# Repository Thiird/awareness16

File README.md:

# Awareness16
Mechanical macropad, used as pathfinder for my first custom mechanical keyboard build.  

**SPECS**  
-16 1U keys in a 4x4 matrix, MX footprint

-USB C, CtoC compatible

-RGB Matrix, 6028 SMD LEDs 

-RGB underglow, SK6812MINI-E SMD LEDs

-ESD protection

-MCU: Atmega 32u4, TQFP44 package

-LED driver: IS31FL3733, eTQFP-48 package

# Renderings

**PCB top**

**PCB bottom**

# Credits
Without the help of many generous and patient people online I would have never been able to complete
this project.

Special thanks to:
- Hadi for making a pcb guide series: https://www.youtube.com/channel/UCpWGAJr2AU7LPUwVYbBQZRg
- People on the Keyboard Atelier discord
- People on the QMK discord

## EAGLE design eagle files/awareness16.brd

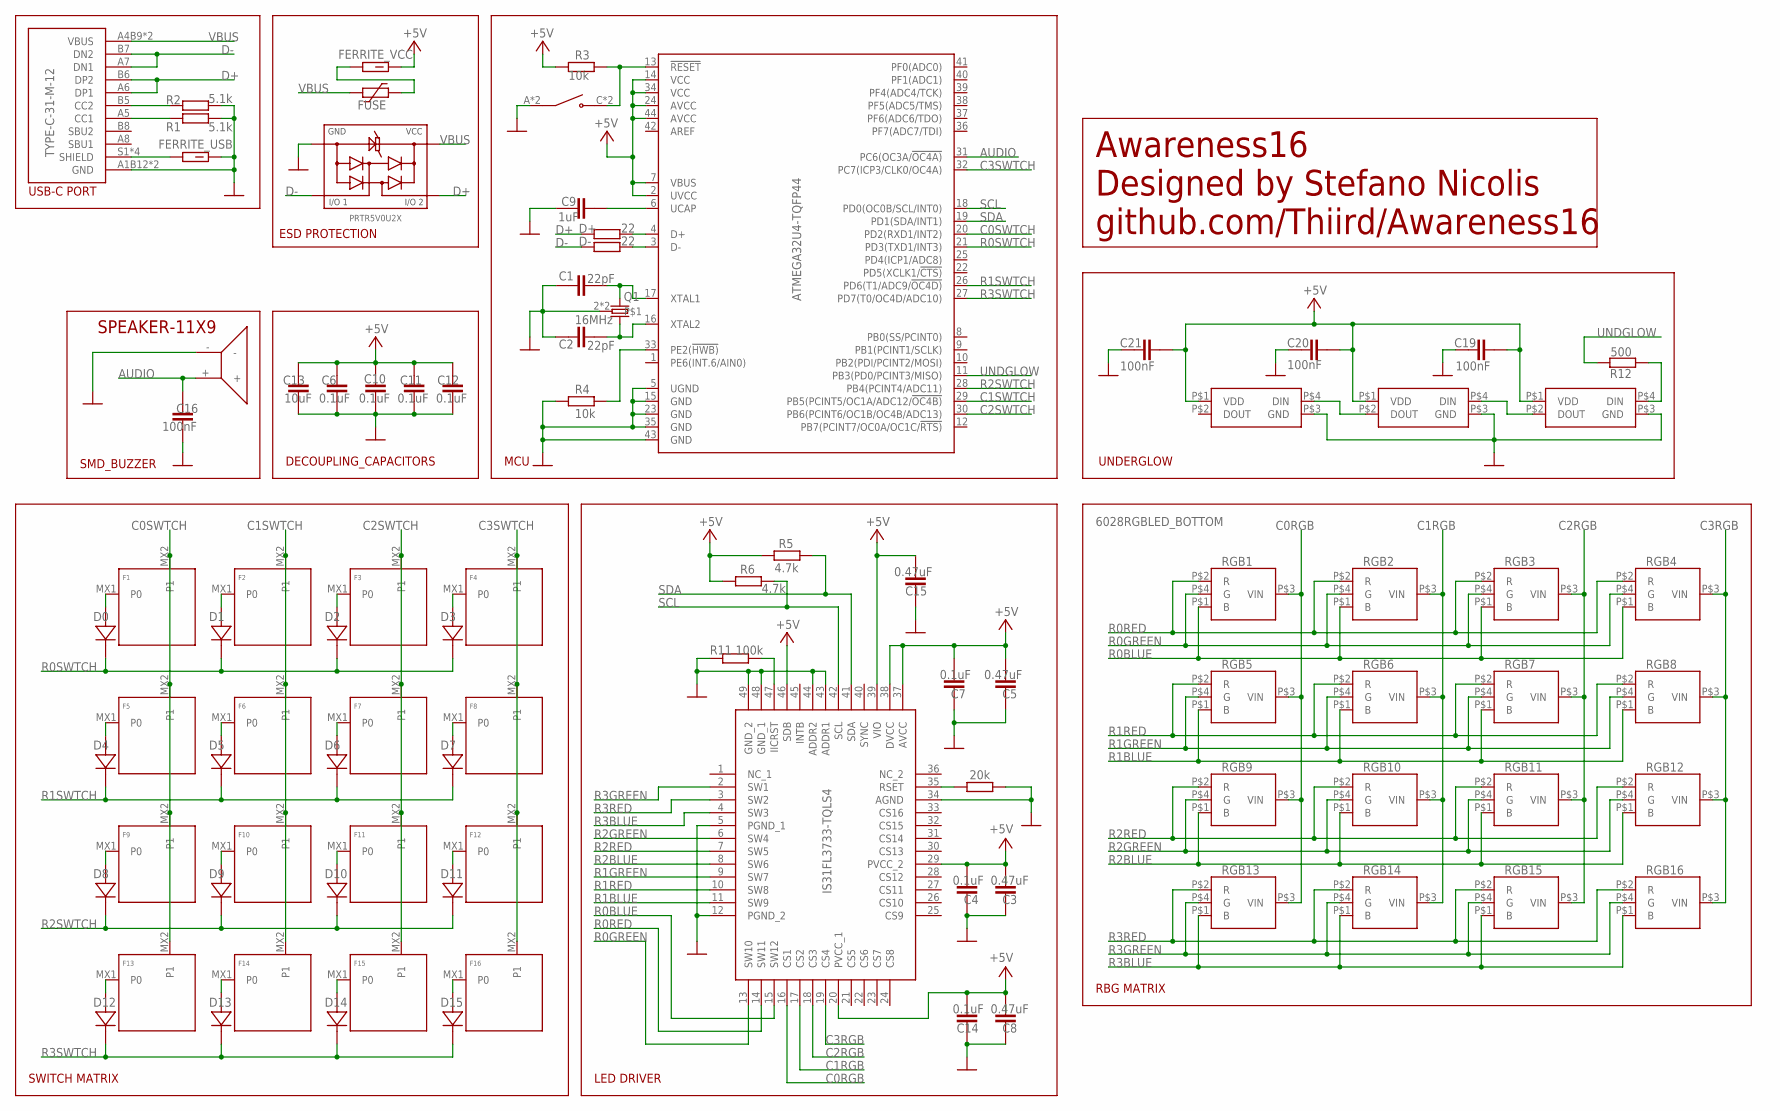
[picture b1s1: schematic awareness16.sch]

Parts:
C1, C2: 22pF; C0603
C3, C5, C8, C15: 0.47uF; C0603
C4, C6, C7, C10, C11, C12, C14: 0.1uF; C0603
C9: 1uF; C0603
C13: 10uF; C0603
C16, C19, C20, C21: 100nF; C0603
D0, D1, D2, D3, D4, D5, D6, D7, D8, D9, D10, D11, D12, D13, D14, D15: DIODE-SOD-123; SOD-123
D+: 22; R0603
D-: 22; R0603
DRIVER: IS31FL3733-TQLS4; QFP50P900X900X120-49N
F1, F2, F3, F4, F5, F6, F7, F8, F9, F10, F11, F12, F13, F14, F15, F16: KEYSWITCH-PLAIN-MX-1U; MX-1U
FERRITE_USB: FERRITE_BEAD; BEADC1608X95N
FERRITE_VCC: FERRITE_BEAD; BEADC1608X95N
FUSE: 0603L050; 0603L
J1: TYPE-C-31-M-12; HRO_TYPE-C-31-M-12
MCU: ATMEGA32U4-TQFP44; TQFP44-0.8-9.6X9.6MM
Q1: 16MHz; 2.0X1.6_KX-5
R1, R2: 5.1k; R0603
R3, R4: 10k; R0603
R5, R6: 4.7k; R0603
R11: 100k; R0603
R12: 500; R0603
RESET: 20k; R0603
RGB1, RGB2, RGB3, RGB4, RGB5, RGB6, RGB7, RGB8, RGB9, RGB10, RGB11, RGB12, RGB13, RGB14, RGB15, RGB16: 6028RGBLED_BOTTOM
S1: TS-1187A-B-A-B; SW_TS-1187A-B-A-B
SP1: SPEAKER-11X9; AST1109MLTRQ
U$1: PRTR5V0U2X
UGLOW1, UGLOW2, UGLOW3: SK6812MINI-E

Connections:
AUDIO: C16.1, MCU.31 (PC6(OC3A/!OC4A)), SP1.+
C0RGB: DRIVER.16 (CS1), RGB1.P$3 (VIN), RGB5.P$3 (VIN), RGB9.P$3 (VIN), RGB13.P$3 (VIN)
C0SWTCH: F1.MX2 (P1), F5.MX2 (P1), F9.MX2 (P1), F13.MX2 (P1), MCU.20 (PD2(RXD1/INT2))
C1RGB: DRIVER.17 (CS2), RGB2.P$3 (VIN), RGB6.P$3 (VIN), RGB10.P$3 (VIN), RGB14.P$3 (VIN)
C1SWTCH: F2.MX2 (P1), F6.MX2 (P1), F10.MX2 (P1), F14.MX2 (P1), MCU.29 (PB5(PCINT5/OC1A/ADC12/!OC4B))
C2RGB: DRIVER.18 (CS3), RGB3.P$3 (VIN), RGB7.P$3 (VIN), RGB11.P$3 (VIN), RGB15.P$3 (VIN)
C2SWTCH: F3.MX2 (P1), F7.MX2 (P1), F11.MX2 (P1), F15.MX2 (P1), MCU.30 (PB6(PCINT6/OC1B/OC4B/ADC13))
C3RGB: DRIVER.19 (CS4), RGB4.P$3 (VIN), RGB8.P$3 (VIN), RGB12.P$3 (VIN), RGB16.P$3 (VIN)
C3SWTCH: F4.MX2 (P1), F8.MX2 (P1), F12.MX2 (P1), F16.MX2 (P1), MCU.32 (PC7(ICP3/CLK0/OC4A))
D+: D+.1, J1.A6 (DP1), J1.B6 (DP2), U$1.3
D-: D-.1, J1.A7 (DN1), J1.B7 (DN2), U$1.2
GND: C1.1, C2.1, C3.1, C4.1, C5.1, C6.2, C7.1, C8.1, C9.1, C10.2, C11.2, C12.2, C13.2, C14.1, C15.1, C16.2, C19.1, C20.1, C21.1, DRIVER.5 (PGND_1), DRIVER.12 (PGND_2), DRIVER.34 (AGND), DRIVER.43 (ADDR1), DRIVER.44 (ADDR2), DRIVER.48 (GND_1), DRIVER.49 (GND_2), FERRITE_USB.2, J1.A1B12 (GND), J1.B1A12 (GND), MCU.5 (UGND), MCU.15 (GND), MCU.23 (GND), MCU.35 (GND), MCU.43 (GND), Q1.2, Q1.4, R1.1, R2.1, R4.1, R11.1, RESET.2, S1.A (COM), S1.B (COM), SP1.-, U$1.1, UGLOW1.P$3 (GND), UGLOW2.P$3 (GND), UGLOW3.P$3 (GND)
unnamed: D0.A, F1.MX1 (P0)
unnamed: FERRITE_VCC.1, FUSE.1
unnamed: D1.A, F2.MX1 (P0)
unnamed: D2.A, F3.MX1 (P0)
unnamed: C2.2, MCU.16 (XTAL2), Q1.3 (2)
unnamed: D-.2, MCU.3 (D-)
unnamed: R12.1, UGLOW3.P$4 (DIN)
unnamed: MCU.33 (PE2(!HWB)), R4.2
unnamed: D4.A, F5.MX1 (P0)
unnamed: DRIVER.47 (IICRST), R11.2
unnamed: D5.A, F6.MX1 (P0)
unnamed: D6.A, F7.MX1 (P0)
unnamed: D9.A, F10.MX1 (P0)
unnamed: D+.2, MCU.4 (D+)
unnamed: MCU.13 (!RESET), R3.2, S1.C (NO), S1.D (NO)
unnamed: C9.2, MCU.6 (UCAP)
unnamed: C1.2, MCU.17 (XTAL1), Q1.1
unnamed: D10.A, F11.MX1 (P0)
unnamed: FERRITE_USB.1, J1.A5 (CC1), J1.B5 (CC2), J1.S1 (SHIELD), J1.S2 (SHIELD), J1.S3 (SHIELD), J1.S4 (SHIELD), R1.2, R2.2
unnamed: UGLOW1.P$4 (DIN), UGLOW2.P$2 (DOUT)
unnamed: DRIVER.35 (RSET), RESET.1
unnamed: D3.A, F4.MX1 (P0)
unnamed: D7.A, F8.MX1 (P0)
unnamed: D11.A, F12.MX1 (P0)
unnamed: D13.A, F14.MX1 (P0)
unnamed: D14.A, F15.MX1 (P0)
unnamed: D12.A, F13.MX1 (P0)
unnamed: D15.A, F16.MX1 (P0)
unnamed: D8.A, F9.MX1 (P0)
unnamed: UGLOW2.P$4 (DIN), UGLOW3.P$2 (DOUT)
R0BLUE: DRIVER.15 (SW12), RGB1.P$1 (B), RGB2.P$1 (B), RGB3.P$1 (B), RGB4.P$1 (B)
R0GREEN: DRIVER.13 (SW10), RGB1.P$4 (G), RGB2.P$4 (G), RGB3.P$4 (G), RGB4.P$4 (G)
R0RED: DRIVER.14 (SW11), RGB1.P$2 (R), RGB2.P$2 (R), RGB3.P$2 (R), RGB4.P$2 (R)
R0SWTCH: D0.C, D1.C, D2.C, D3.C, MCU.21 (PD3(TXD1/INT3))
R1BLUE: DRIVER.11 (SW9), RGB5.P$1 (B), RGB6.P$1 (B), RGB7.P$1 (B), RGB8.P$1 (B)
R1GREEN: DRIVER.9 (SW7), RGB5.P$4 (G), RGB6.P$4 (G), RGB7.P$4 (G), RGB8.P$4 (G)
R1RED: DRIVER.10 (SW8), RGB5.P$2 (R), RGB6.P$2 (R), RGB7.P$2 (R), RGB8.P$2 (R)
R1SWTCH: D4.C, D5.C, D6.C, D7.C, MCU.26 (PD6(T1/ADC9/!OC4D))
R2BLUE: DRIVER.8 (SW6), RGB9.P$1 (B), RGB10.P$1 (B), RGB11.P$1 (B), RGB12.P$1 (B)
R2GREEN: DRIVER.6 (SW4), RGB9.P$4 (G), RGB10.P$4 (G), RGB11.P$4 (G), RGB12.P$4 (G)
R2RED: DRIVER.7 (SW5), RGB9.P$2 (R), RGB10.P$2 (R), RGB11.P$2 (R), RGB12.P$2 (R)
R2SWTCH: D8.C, D9.C, D10.C, D11.C, MCU.28 (PB4(PCINT4/ADC11))
R3BLUE: DRIVER.4 (SW3), RGB13.P$1 (B), RGB14.P$1 (B), RGB15.P$1 (B), RGB16.P$1 (B)
R3GREEN: DRIVER.2 (SW1), RGB13.P$4 (G), RGB14.P$4 (G), RGB15.P$4 (G), RGB16.P$4 (G)
R3RED: DRIVER.3 (SW2), RGB13.P$2 (R), RGB14.P$2 (R), RGB15.P$2 (R), RGB16.P$2 (R)
R3SWTCH: D12.C, D13.C, D14.C, D15.C, MCU.27 (PD7(T0/OC4D/ADC10))
SCL: DRIVER.42 (SCL), MCU.18 (PD0(OC0B/SCL/INT0)), R6.1
SDA: DRIVER.41 (SDA), MCU.19 (PD1(SDA/INT1)), R5.1
UNDGLOW: MCU.11 (PB3(PD0/PCINT3/MISO)), R12.2
VBUS: FUSE.2, J1.A4B9 (VBUS), J1.B4A9 (VBUS), U$1.4
VCC: C3.2, C4.2, C5.2, C6.1, C7.2, C8.2, C10.1, C11.1, C12.1, C13.1, C14.2, C15.2, C19.2, C20.2, C21.2, DRIVER.20 (PVCC_1), DRIVER.29 (PVCC_2), DRIVER.37 (AVCC), DRIVER.38 (DVCC), DRIVER.39 (VIO), DRIVER.46 (SDB), FERRITE_VCC.2, MCU.2 (UVCC), MCU.7 (VBUS), MCU.14 (VCC), MCU.24 (AVCC), MCU.34 (VCC), MCU.44 (AVCC), R3.1, R5.2, R6.2, UGLOW1.P$1 (VDD), UGLOW2.P$1 (VDD), UGLOW3.P$1 (VDD)

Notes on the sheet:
MCU
UNDERGLOW
SWITCH MATRIX
RBG MATRIX
ESD PROTECTION
DECOUPLING_CAPACITORS
LED DRIVER
SMD_BUZZER
USB-C PORT
Awareness16 Designed by Stefano Nicolis github.com/Thiird/Awareness16

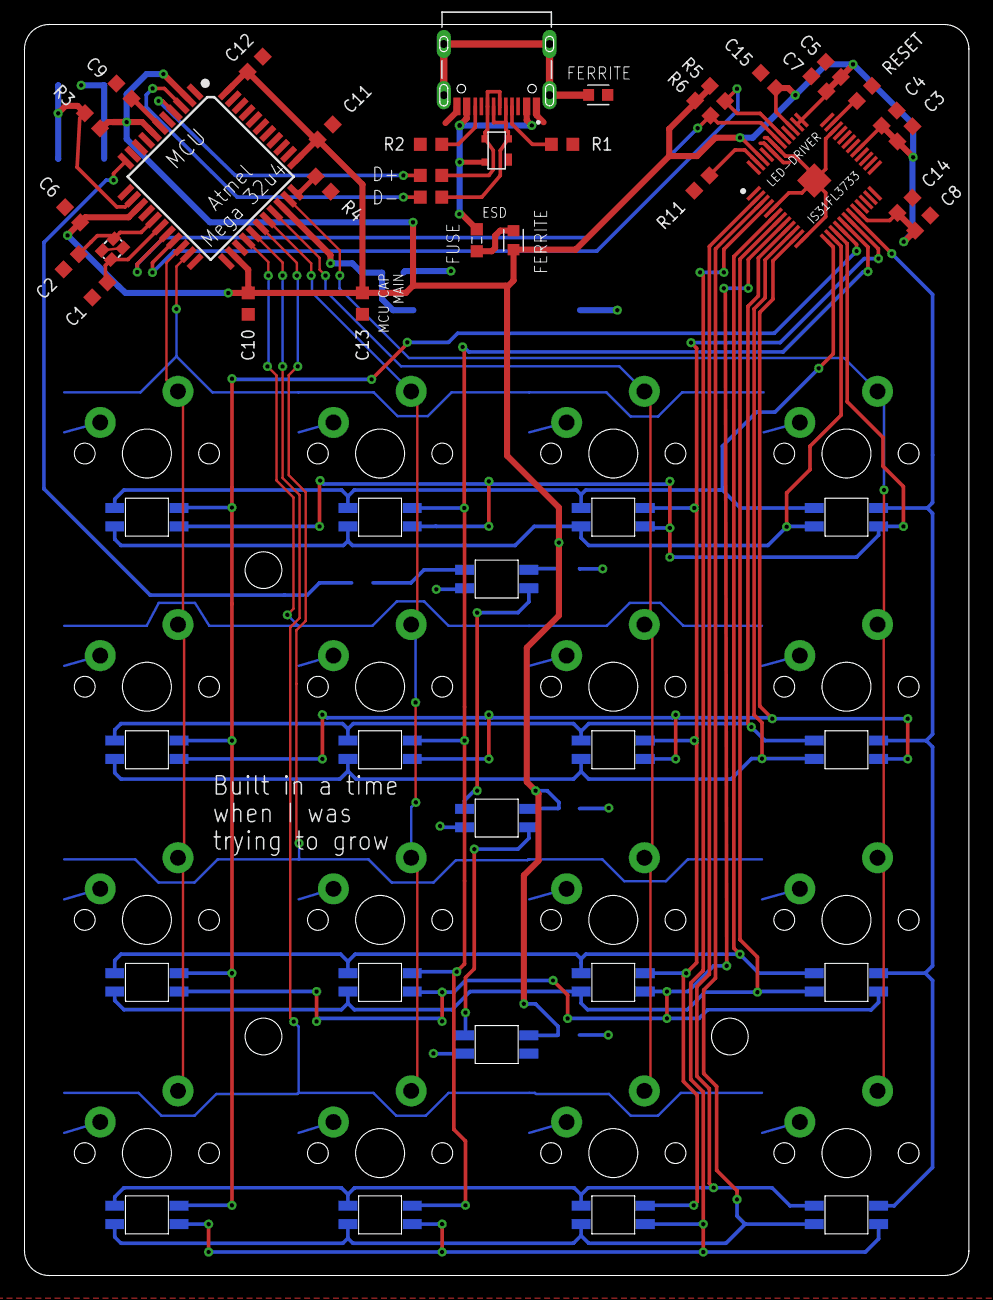
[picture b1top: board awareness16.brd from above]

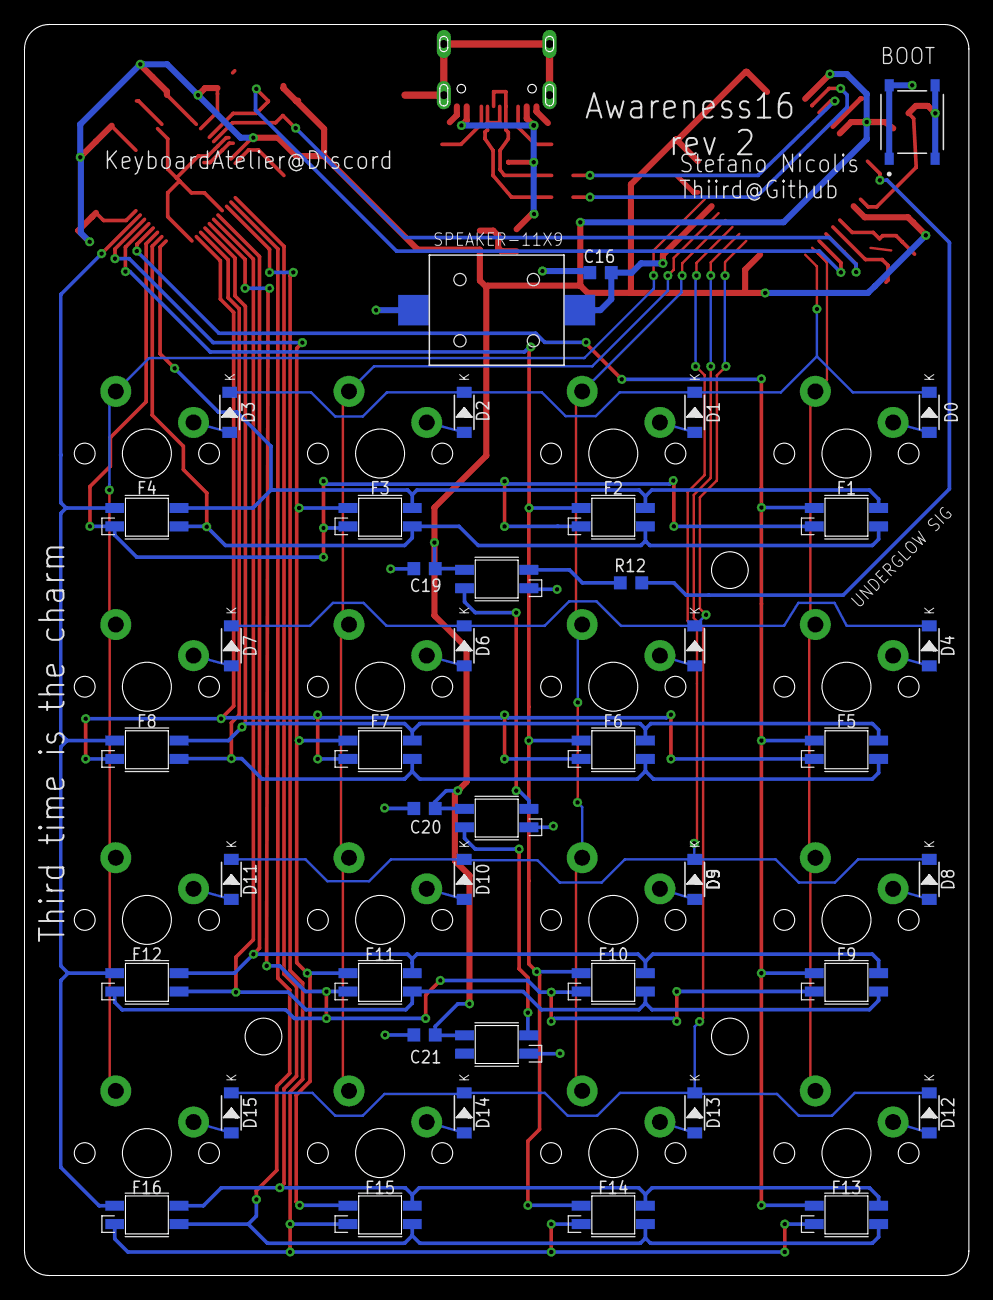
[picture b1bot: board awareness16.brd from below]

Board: 2 copper layers, 77.2 x 102.2 mm, 91 parts (26 on the bottom side), 63 nets.

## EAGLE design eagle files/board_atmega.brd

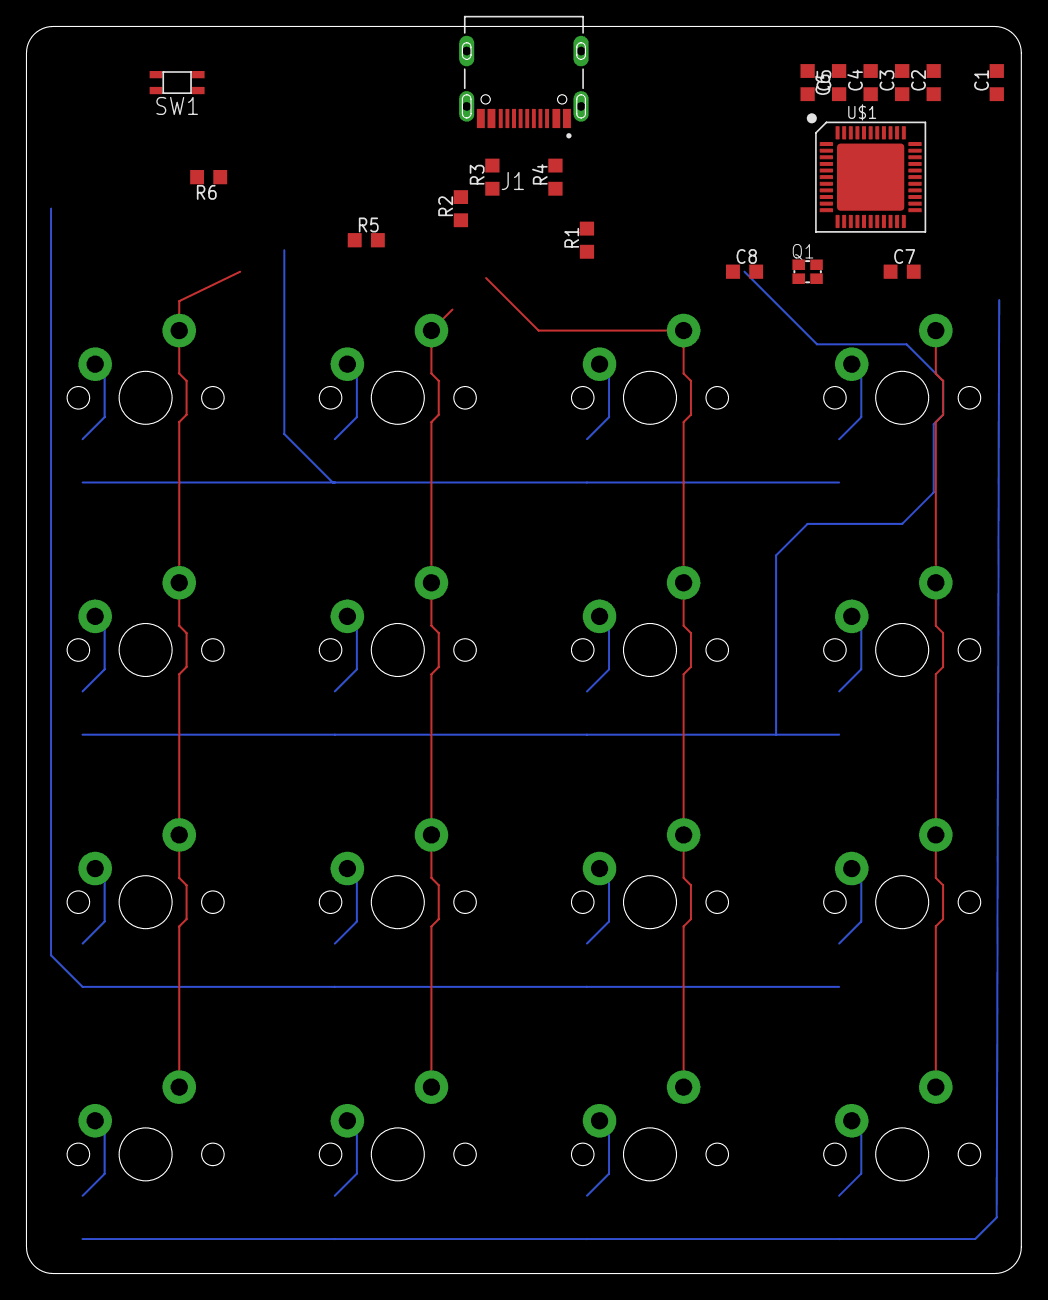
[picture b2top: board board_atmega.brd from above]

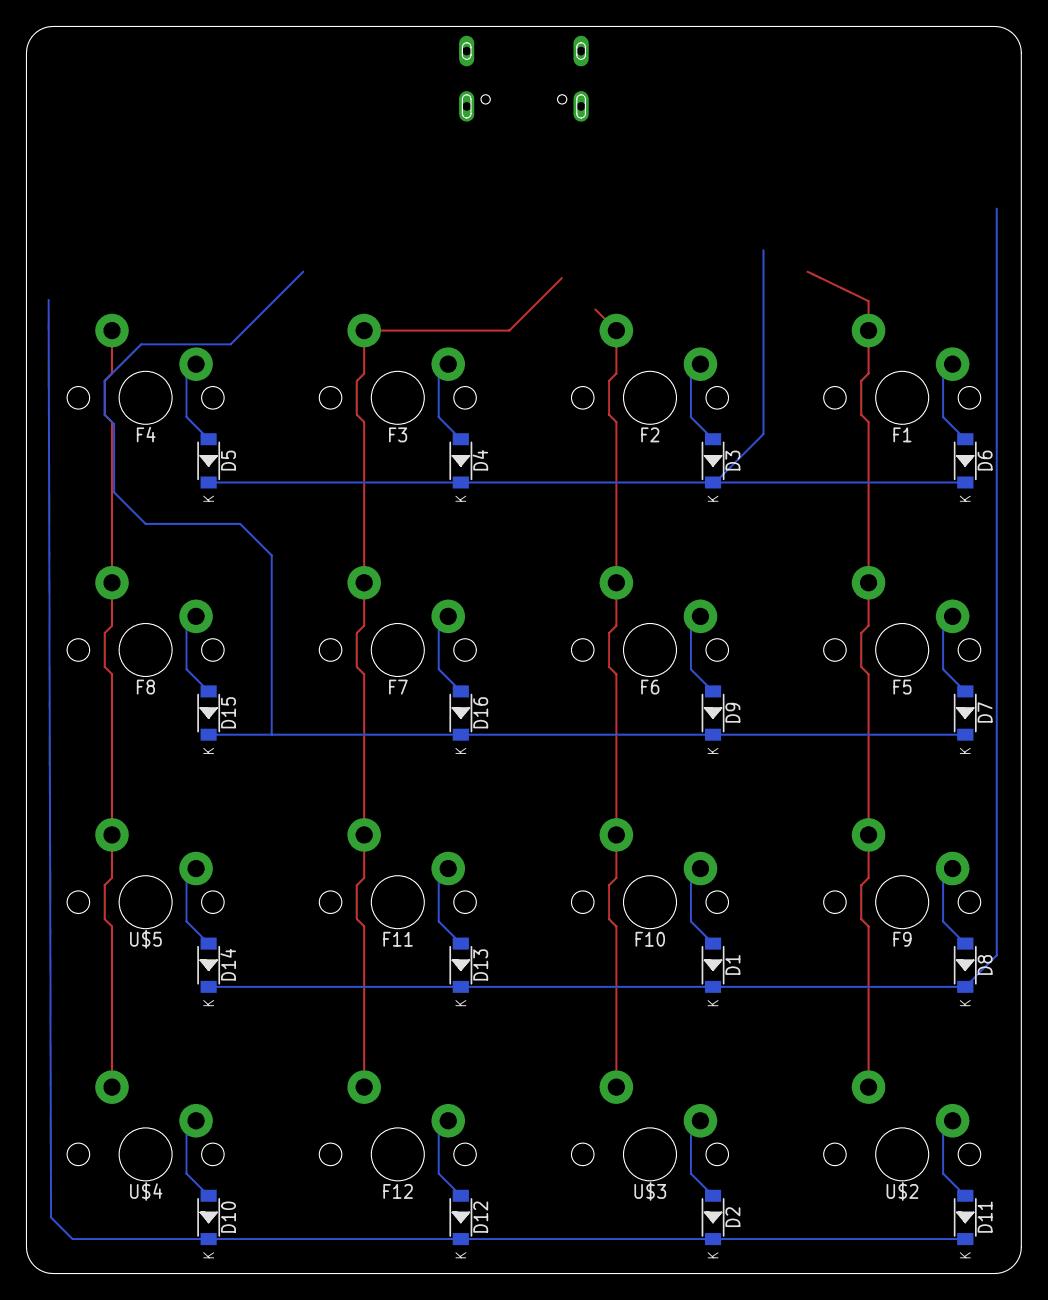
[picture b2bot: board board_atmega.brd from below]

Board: 2 copper layers, 75.2 x 94.2 mm, 50 parts (16 on the bottom side), 37 nets.

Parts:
C1, C2, C3, C4: 0.1uF; C0603
C5: 10uF; C0603
C6: 1uF; C0603
C7, C8: 22uF; C0603
D1, D2, D3, D4, D5, D6, D7, D8, D9, D10, D11, D12, D13, D14, D15, D16: SOD-123
F1, F2, F3, F4, F5, F6, F7, F8, F9, F10, F11, F12: KEYSWITCH-PLAIN-MX-1U; MX-1U
J1: TYPE-C-31-M-12; HRO_TYPE-C-31-M-12
Q1: 16Mhz; 2.0X1.6_KX-5
R1, R2: 5.1k; R0603
R3, R4: 22; R0603
R5, R6: 10k; R0603
SW1: SWITCH-SMD-EVP-BB2A9B00
U$1: ATMEGA32U4-QFN44; QFN-44
U$2, U$3, U$4, U$5: KEYSWITCH-PLAIN-MX-1U; MX-1U

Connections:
0: C1.2, C2.2, C3.2, C4.2, C5.2, C6.1, C7.1, C8.1, J1.A1B12, J1.B1A12, J1.S1, J1.S2, J1.S3, J1.S4, R1.1, R2.1, R6.1, SW1.A@1, SW1.A@2, U$1.5, U$1.15, U$1.23, U$1.35, U$1.43, U$1.TAB
C0: F1.MX2, F5.MX2, F9.MX2, U$2.MX2
C1: F2.MX2, F6.MX2, F10.MX2, U$3.MX2
C2: F3.MX2, F7.MX2, F11.MX2, F12.MX2
C3: F4.MX2, F8.MX2, U$4.MX2, U$5.MX2
D+: J1.A6, J1.B6, R4.1
D-: J1.A7, J1.B7, R3.1
unnamed: D6.A, F1.MX1
unnamed: D3.A, F2.MX1
unnamed: D4.A, F3.MX1
unnamed: D5.A, F4.MX1
unnamed: D7.A, F5.MX1
unnamed: D9.A, F6.MX1
unnamed: D16.A, F7.MX1
unnamed: D8.A, F9.MX1
unnamed: D1.A, F10.MX1
unnamed: D13.A, F11.MX1
unnamed: D12.A, F12.MX1
unnamed: D11.A, U$2.MX1
unnamed: D14.A, U$5.MX1
unnamed: D15.A, F8.MX1
unnamed: J1.B5, R2.2
unnamed: J1.A5, R1.2
unnamed: R6.2, U$1.33
unnamed: C6.2, U$1.6
unnamed: C7.2, Q1.3, U$1.17
unnamed: R3.2, U$1.3
unnamed: R4.2, U$1.4
unnamed: C8.2, Q1.1, U$1.16
unnamed: D10.A, U$4.MX1
unnamed: R5.2, SW1.B@3, SW1.B@4, U$1.13
unnamed: D2.A, U$3.MX1
R0: D3.C, D4.C, D5.C, D6.C
R1: D7.C, D9.C, D15.C, D16.C
R2: D1.C, D8.C, D13.C, D14.C
R3: D2.C, D10.C, D11.C, D12.C
VCC: C1.1, C2.1, C3.1, C4.1, C5.1, J1.A4B9, J1.B4A9, R5.1, U$1.2, U$1.7, U$1.14, U$1.24, U$1.34, U$1.44

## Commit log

2020-10-18 schematic and board files added
2020-10-19 Added underglow WS2812B LEDs
2020-10-23 New SK6812MINI-E footprint, added ground pin on crystal, fixed misconnections
2020-10-24 started board, added rgb matrix
2020-10-25 ESD protection, dxf board-switch matrix reference, started routing
2020-10-27 Board layout progress
2020-10-29 ESD Finished, led driver work, board placement work
2020-10-30 Led driver finished, usb footprint made unilateral and fixed D+ D- connection, board work
2020-10-31 Major board routing, GND net fix
2020-11-01 Board USB are work, minor fixes
2020-11-01 GND net fixes, drc checks, other fixes
2020-11-02 ESD routing fix and finished, usb data line resistors moved after ESD, minor fixes
2020-11-07 Routing fixes
2020-11-08 Added rendering folder, enlargerd gnd plane, traces width corrected
2020-11-10 Small routing fixes, added credits in sch and brd
2020-11-11 Led driver connections to leds fixed in sch and brd
2020-11-13 brd minor fixes
2020-11-16 Enlarged pcb on top for case matching, re routed to accomodate this change
2020-11-19 Small board fixes
2020-12-24 Fixed xtal caps value and missing C4 name on brd
2020-12-29 Component font size, routing adjustments
2021-03-14 Rev 1 start
2021-03-14 Fixed gnd plane not reaching underglow led #3, routing revision
2021-03-15 Backlight led footprint fixed, started rerouting of those and other routing fixes
2021-03-16 Rgb matrix leds routing done, underglow leds routing done
2021-03-18 REV 1 final commit
2021-04-25 Revision 2, added a decent bootloader button on back of board, routing fixes
2021-05-19 Repo clean up, readme update
2021-05-23 Minor board adjustments

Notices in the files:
parts and their libraries:
crystal-geyer_V1_0_NIC: Copyright: Geyer-Electronic
